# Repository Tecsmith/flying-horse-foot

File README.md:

# The Flying Horse Foot

This body of work is my attempt to build a clone of "The Pegasus Hoof" keyboard controller.

This came about because some time ago I'd bought a Filco MJ2 TLK mechanical keyboard with the intent to use it as a basis of a custom build Mechanical Board ... alas, other things had priority and 7 years later I found that I could no longer buy the hacker controller - "The Pegasus Hoof" - by Fredrik Atmer of ["Bathroom Epiphanies Inc."](http://bathroomepiphanies.com/controllers/)

### Why?

I use Mac ... the Filco Majestouch 2 Tenkeyless *(also Filco Majestouch 87/88 and Filco Zero)* has Windows key-mapping (i.e., `Ctrl`, `Win`, `Alt`), and I want MacOS key-mapping (i.e., `Ctrl`, `Option` *(Alt)*, `Command`).

## Copyright

The original "The Pegasus Hoof" was a keyboard controller developed by Fredrik Atmer of ["Bathroom Epiphanies Inc."](http://bathroomepiphanies.com/controllers/)

* Rev. 20131001, *a.k.a. V1*, (c) 2013 Fredrik Atmer
* Rev. 20150108, *a.k.a. V2*, (c) 2015 Fredrik Atmer

This work is:

* Rev. 20210911, *a.k.a. V3.1*, by Silvino Rodrigues, no copyright claimed
*  Attribution remains (c) 2015 Fredrik Atmer

See: [LICENSE.md](LICENSE.md)

## This Revision *(v3.1)*

This revision is schematically equivalent to (v2) **Rev. 20150108**, with a few additional features:

1. An SPI6 AVR programming header is added for easier flashing - do not populate these pins on a deployed keyboard.
   * These are not in the standard 2x3 SPI header, but rather a 1x6 inline header so that one can use them as pogo-holes.
   * Follow the instructions at the [QMK - ISP Flashing Guide](https://beta.docs.qmk.fm/using-qmk/guides/keyboard-building/isp_flashing_guide) docs page.
2. There are 3 hardware reset options:
   * The original magnetic reed-switch option is available, can be disabled to prevent unintended resets once the keyboard is deployed - scratch off the trace between JP1 to disconnect the reed switch from the circuit.
   * A reset 0.1-inch 2-pin set is provided for easy resets during programming - short the pins with a tweezer or similar.
   * An optional physical switch can be added to the board for press-button resetting.
3. Added an optional ESD protection circuit ensuring the inbound USB line cannot damage the board.

  &nbsp; 

## Firmware

### Adaptation

The [Firmware/](Firmware) folder has an adaptation that will work with QMK compiling to a VIA binary.  This can then used with VIA and a side-load JSON file, also provided.

The included source is confirmed to be working - but only supports the ANSI layout, and mapped to MacOS keyboard (WIN + ALT keys are swapped to OPT + COM).

### Originals

There are a few choices:

* Fredrik's **epiphanies_qmk_keyboard** - https://github.com/BathroomEpiphanies/epiphanies_qmk_keyboard *(requires QMK)*
  * **QMK** - https://github.com/qmk/qmk_firmware
  * See also: https://github.com/qmk/qmk_firmware/tree/master/keyboards/bpiphany/pegasushoof/ *(Use the 2015 variant)*
  * Also try the online configurator - https://config.qmk.fm/#/bpiphany/pegasushoof/2015/LAYOUT
* Fredrik's **epiphanies_tmk_keyboard** - https://github.com/BathroomEpiphanies/epiphanies_tmk_keyboard *(requires TMK)*
  * Hasu's **TMK** - https://github.com/tmk/tmk_keyboard
* David Howland's *(a.k.a. "metalliqaz")* **EasyAVR** - https://github.com/dhowland/EasyAVR
* Fredrik's **costar_keyboard** - https://github.com/BathroomEpiphanies/costar_keyboard *(original, older)*

*(For all above use the 2015 / v2 variant of The Pegasus Hoof)*

### Flashing

The default boot loader does not support flashing from USB *(or if it does I can't find a how to)*.  As such one will need to use the supplied ISP pins and flash the board with an ISP programer like the [USBasp](https://www.fischl.de/usbasp/).

----------

## Build your own

### PCB

Using the included [Gerber](Gerber/) files, you can have this board made for you from a prototype manufacturer.

I have used the following with great success:

* [JLCPCB](https://jlcpcb.com/) *(V3.1 was made by JLCPCB on purple FR4 - love the look, and PCB is impeccable.)*
* [Smart-Prototyping](https://www.smart-prototyping.com/)  *(V3.0 board was flawlessly manufactured, albeit with a trace error that I'd overlooked the design.  I'd used black PCB and it remains my preferred colour.)*
* but there are others, like:  PCBWay, OSHPark, Seeedstudio

### Hardware / Part List

| Qty | Description                 | Size      | Mnf. Part No.         | Mouser PN            | Element14 PN | Spec. |
|-----|-----------------------------|-----------|-----------------------|----------------------|--------------|-------|
|  1  | ATmega32u2 micro controller | TQFP32    | ATMEGA32U2-AU         | 556-ATMEGA32U2-AU    | 1748524      | [&#128196;](DataSheets/01__ATmega32u2.pdf) |
|  2  | 4-10 Decoder Logic IC       | SOIC      | SN74HC42DR            | 595-SN74HC42DR       | 3119918      | [&#128196;](DataSheets/02__74HC42.pdf) |
|  1  | 16MHz crystal oscillator    | 3.2x2.5mm | CX3225SB16000E0EGFCC  | 581-CX3225SB16000EGF | *-- n/a --*  | [&#128196;](DataSheets/03a_SB16000E0.pdf) |
|     |   " *(alt)*                 |           | ABM8G-16.000MHZ-4Y-T3 | *-- n/a --*          | 2467842      | [&#128196;](DataSheets/03b_ABM8G_16MHZ.pdf) |
|  1  | 10µF electrolytic capacitor | 4.3x5.5mm | EEE-1CA100SR          | 667-EEE-1CA100SR     | 9696920      | [&#128196;](DataSheets/04__1CA100SR.pdf) |
|  2  | 18pF ceramic capacitors     | 0603      | C1608C0G1H180J080AA   | 810-C1608C0G1H180J   | 1907287      |       |
|  3  | 100nF ceramic capacitors    | 0603      | C1608X7R1E104K080AA   | 810-C1608X7R1E104K   | 2332586      |       |
|  2  | 1µF ceramic capacitors      | 0603      | C1608X7R1C105K080AC   | 810-C1608X7R1C105K   | 1907343      |       |
|  2  | 22Ω resistors               | 0603      | ERJ-3GEYJ220V         | 667-ERJ-3GEYJ220V    | 2059557      |       |
|  4  | 10kΩ resistors              | 0603      | ERJ-3GEYJ103V         | 667-ERJ-3GEYJ103V    | 2059627      |       |
|  2  | 18-pin headers, 2mm pitch   | 2mm pitch | M22-2011205           | 855-M22-2011805      | 3395122      | [Better Option](https://www.adafruit.com/product/2671) |
| ~1~ | Magnetic Reed Switch        | 15mm      | MK06-5-B              | 876-MK6-5-B          | 1079479      | [&#128196;](DataSheets/05__MK06_V02.pdf) |
| ~1~ | ESD Protection Device       | SOT-23    | TPD4S009DBVR          | 595-TPD4S009DBVR     | 3116519      | [&#128196;](DataSheets/06__tpd4s009.pdf) |
| ~1~ | Compact Tactile Switche     | 3.9x2.9mm | SKRKAEE020            | 688-SKRKAEE020       | *-- n/a --*  | [&#128196;](DataSheets/07__SKRK-1370789.pdf) |

<small>~*~ = items marked with tilde are optional.</small>

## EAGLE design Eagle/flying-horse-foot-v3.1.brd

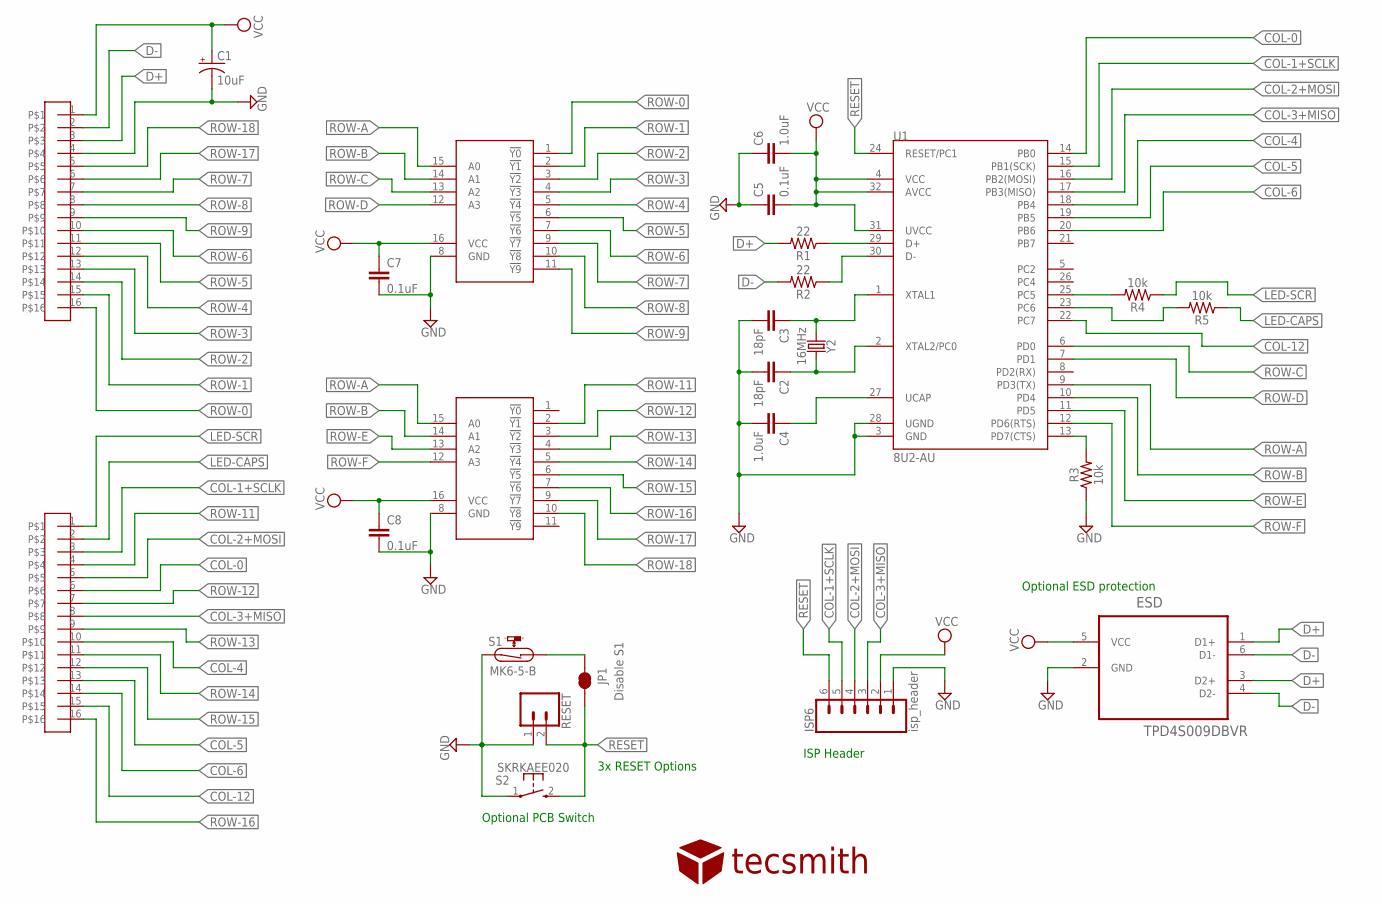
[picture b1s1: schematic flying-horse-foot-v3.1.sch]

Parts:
C1: 10uF; EEE-1CA100SR
C2, C3: 18pF; 0603
C4, C6: 1.0uF; 0603
C5, C7, C8: 0.1uF; 0603
ESD: TPD4S009DBVR; SOT95P280X145-6N
ISP6: isp_header; 1X06_NO_SILK
JP1: Disable S1; SMT-JUMPER_2_NC_TRACE_NO-SILK
R1, R2: 22; 0603
R3, R4, R5: 10k; 0603
RESET: 0.1 inch 2-pin; 1X02
S1: MK6-5-B; MK6-5
S2: SKRKAEE020
U1: 8U2-AU; TQFP32-08_MCU
U$1: SN74HC42DR; D16
U$2: 74HC42D16; D16
U$3, U$4: 16PIN-2MM-HEADER
U$5: TECSMITH-LOGO
Y2: 16MHz; CRYSTAL-SMD-5X3.2-4PAD

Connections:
COL-0: U1.14 (PB0), U$4.6
COL-1+SCLK: ISP6.5, U1.15 (PB1(SCK)), U$4.3
COL-2+MOSI: ISP6.4, U1.16 (PB2(MOSI)), U$4.5
COL-3+MISO: ISP6.3, U1.17 (PB3(MISO)), U$4.8
COL-4: U1.18 (PB4), U$4.10
COL-5: U1.19 (PB5), U$4.13
COL-6: U1.20 (PB6), U$4.14
COL-12: U1.22 (PC7), U$4.15
D+: ESD.1 (D1+), ESD.3 (D2+), R1.2, U$3.3
D-: ESD.4 (D2-), ESD.6 (D1-), R2.2, U$3.2
GND: C1.-, C2.2, C3.2, C4.2, C5.1, C6.1, C7.2, C8.2, ESD.2 (GND), ISP6.1, R3.1, RESET.1, S1.2, S2.1, U1.3 (GND), U1.28 (UGND), U$1.8 (GND), U$2.8 (GND), U$3.4
HWB: R3.2, U1.13 (PD7(CTS))
LED-CAPS: R5.1, U$4.2
LED-SCR: R4.1, U$4.1
unnamed: R1.1, U1.29 (D+)
unnamed: R2.1, U1.30 (D-)
unnamed: C2.1, U1.2 (XTAL2/PC0), Y2.3 (2)
unnamed: C3.1, U1.1 (XTAL1), Y2.1
unnamed: R4.2, U1.25 (PC5)
unnamed: C4.1, U1.27 (UCAP)
unnamed: R5.2, U1.23 (PC6)
unnamed: JP1.1, S1.1
RESET: ISP6.6, JP1.2, RESET.2, S2.2 (3), U1.24 (RESET/PC1)
ROW-0: U$1.1 (!Y0), U$3.16
ROW-1: U$1.2 (!Y1), U$3.15
ROW-2: U$1.3 (!Y2), U$3.14
ROW-3: U$1.4 (!Y3), U$3.13
ROW-4: U$1.5 (!Y4), U$3.12
ROW-5: U$1.6 (!Y5), U$3.11
ROW-6: U$1.7 (!Y6), U$3.10
ROW-7: U$1.9 (!Y7), U$3.7
ROW-8: U$1.10 (!Y8), U$3.8
ROW-9: U$1.11 (!Y9), U$3.9
ROW-11: U$2.2 (!Y1), U$4.4
ROW-12: U$2.3 (!Y2), U$4.7
ROW-13: U$2.4 (!Y3), U$4.9
ROW-14: U$2.5 (!Y4), U$4.11
ROW-15: U$2.6 (!Y5), U$4.12
ROW-16: U$2.7 (!Y6), U$4.16
ROW-17: U$2.9 (!Y7), U$3.6
ROW-18: U$2.10 (!Y8), U$3.5
ROW-A: U1.9 (PD3(TX)), U$1.15 (A0), U$2.15 (A0)
ROW-B: U1.10 (PD4), U$1.14 (A1), U$2.14 (A1)
ROW-C: U1.6 (PD0), U$1.13 (A2)
ROW-D: U1.7 (PD1), U$1.12 (A3)
ROW-E: U1.11 (PD5), U$2.13 (A2)
ROW-F: U1.12 (PD6(RTS)), U$2.12 (A3)
VCC: C1.+, C5.2, C6.2, C7.1, C8.1, ESD.5 (VCC), ISP6.2, U1.4 (VCC), U1.31 (UVCC), U1.32 (AVCC), U$1.16 (VCC), U$2.16 (VCC), U$3.1

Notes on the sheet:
Optional ESD protection
3x RESET Options
Optional PCB Switch
ISP Header

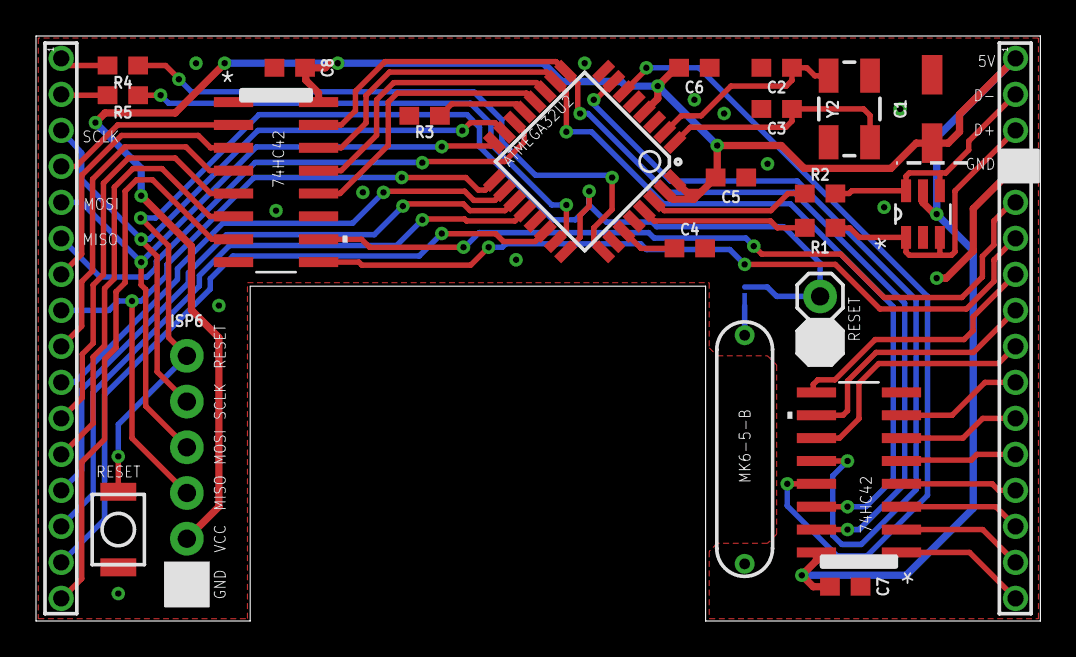
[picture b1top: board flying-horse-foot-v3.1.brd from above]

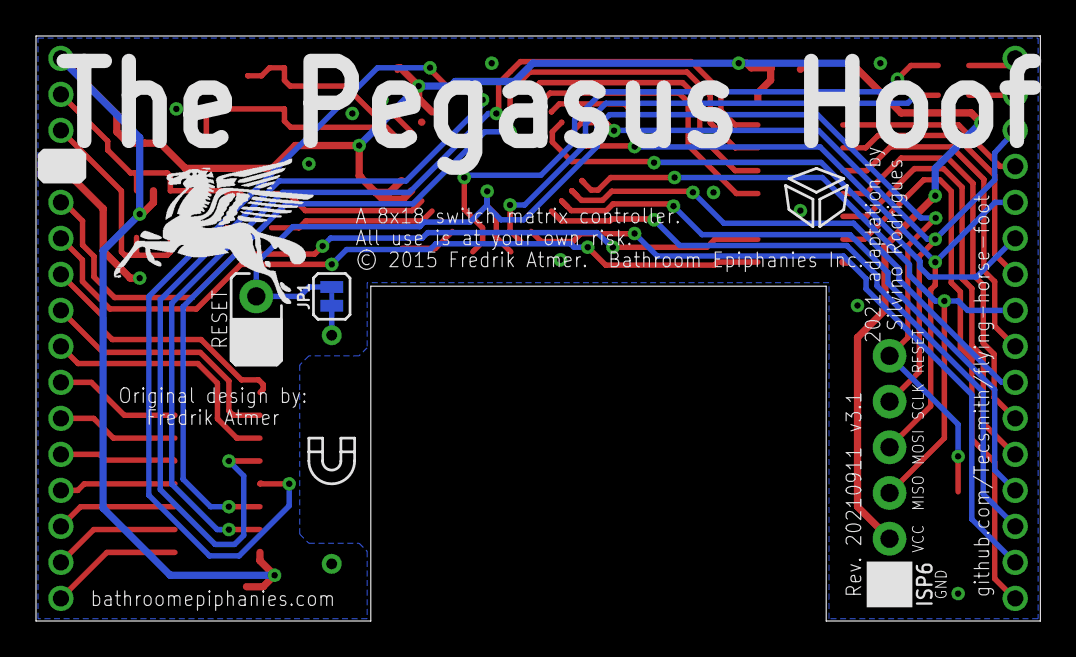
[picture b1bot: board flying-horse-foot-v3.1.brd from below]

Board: 2 copper layers, 55.8 x 32.5 mm, 26 parts (2 on the bottom side), 48 nets.

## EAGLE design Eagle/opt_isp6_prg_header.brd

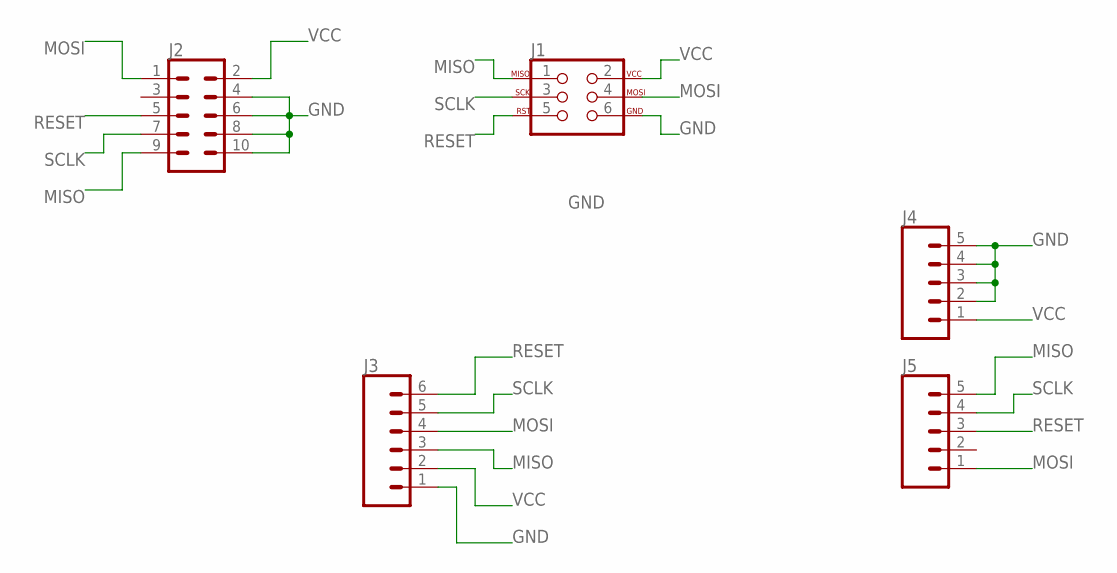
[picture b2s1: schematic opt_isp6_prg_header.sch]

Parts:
J1: AVR_SPI_PROG_3X2NS; 2X3-NS
J2: CONN_05X2SHD; 2X5-SHROUDED
J3: CONN_06NO_SILK_NO_POP; 1X06_NO_SILK
J4, J5: CONN_05VERT_FEMALE_HEADER; 1X05_SMD_VERTICAL_COMBO

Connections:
GND: J1.6, J2.4, J2.6, J2.8, J2.10, J3.1, J4.2, J4.3, J4.4, J4.5
MISO: J1.1, J2.9, J3.3, J5.5
MOSI: J1.4, J2.1, J3.4, J5.1
RESET: J1.5, J2.5, J3.6, J5.3
SCLK: J1.3, J2.7, J3.5, J5.4
VCC: J1.2, J2.2, J3.2, J4.1

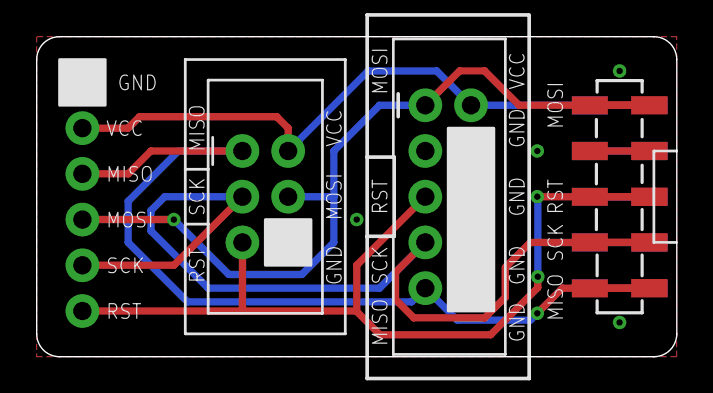
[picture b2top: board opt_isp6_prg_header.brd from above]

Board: 2 copper layers, 35.6 x 17.8 mm, 5 parts (1 on the bottom side), 6 nets.

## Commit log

2021-06-22 initial layout - no traces
2021-06-24 rel 1
2021-06-25 made top plane vcc, instead of gnd
2021-06-26 prep for board manufacturing
2021-06-28 Added SPI6 header for easier AVR programming
2021-06-29 Added jumper to disable magnetic reed switch
2021-06-29 Release 20210625
2021-06-29 updated docs
2021-07-19 first prototype exposed that the headers where over-wide by 0.34mm
2021-07-23 rename with version number
2021-07-26 v3.1 added
2021-09-11 moved from 3x2 SPI header to 6x1 SPI header
2021-09-13 second production run, v3.1
2021-09-13 updated images
2021-09-15 typos
2021-09-15 prod. color = purple
2021-09-15 bonus, ISP programming header
2021-09-22 caps and scr led swap
2021-10-10 It works!
2022-01-05 fixed an incorrect keymap on the right ctrl key
2022-01-05 fixes to VIA keymap

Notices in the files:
Eagle/flying-horse-foot-v3.1.brd:
© 2015 Fredrik Atmer.  Bathroom Epiphanies Inc.
parts and their libraries:
SparkFun-Retired: Licensing: Creative Commons ShareAlike 4.0 International - https://creativecommons.org/licenses/by-sa/4.0
